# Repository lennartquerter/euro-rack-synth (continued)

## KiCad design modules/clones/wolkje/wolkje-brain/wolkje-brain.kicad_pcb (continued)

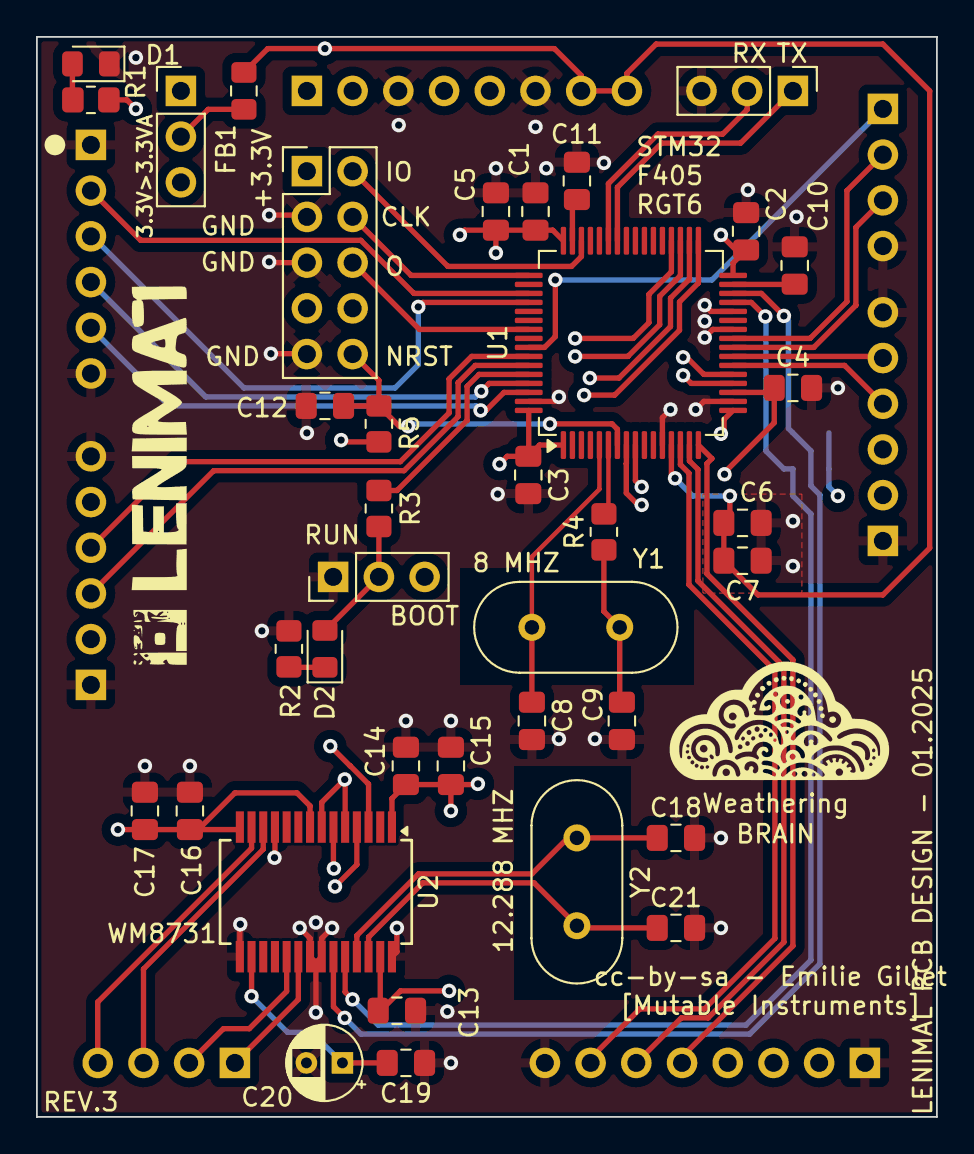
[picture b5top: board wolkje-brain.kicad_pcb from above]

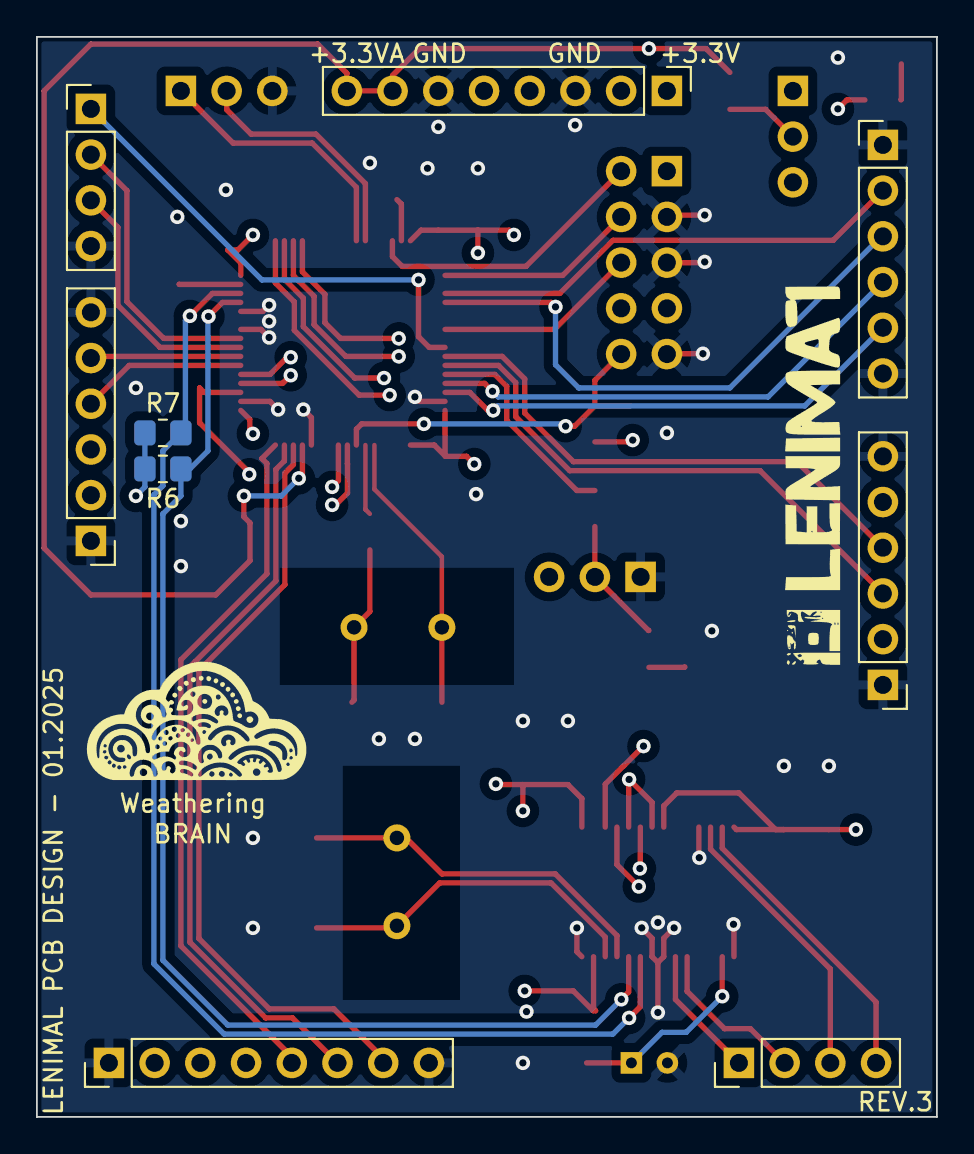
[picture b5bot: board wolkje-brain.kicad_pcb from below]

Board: 4 copper layers, 50.0 x 60.0 mm, 46 parts (9 on the bottom side), 51 nets.

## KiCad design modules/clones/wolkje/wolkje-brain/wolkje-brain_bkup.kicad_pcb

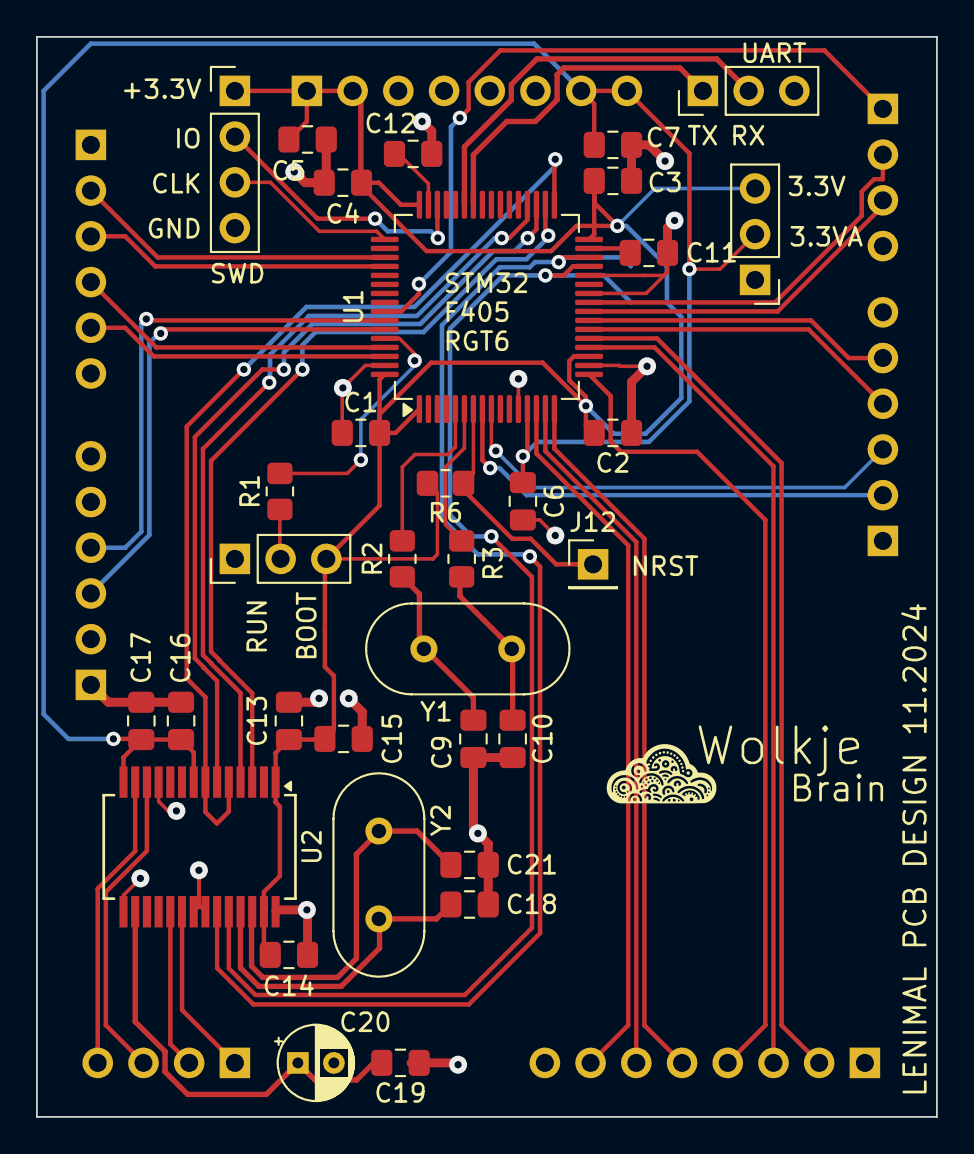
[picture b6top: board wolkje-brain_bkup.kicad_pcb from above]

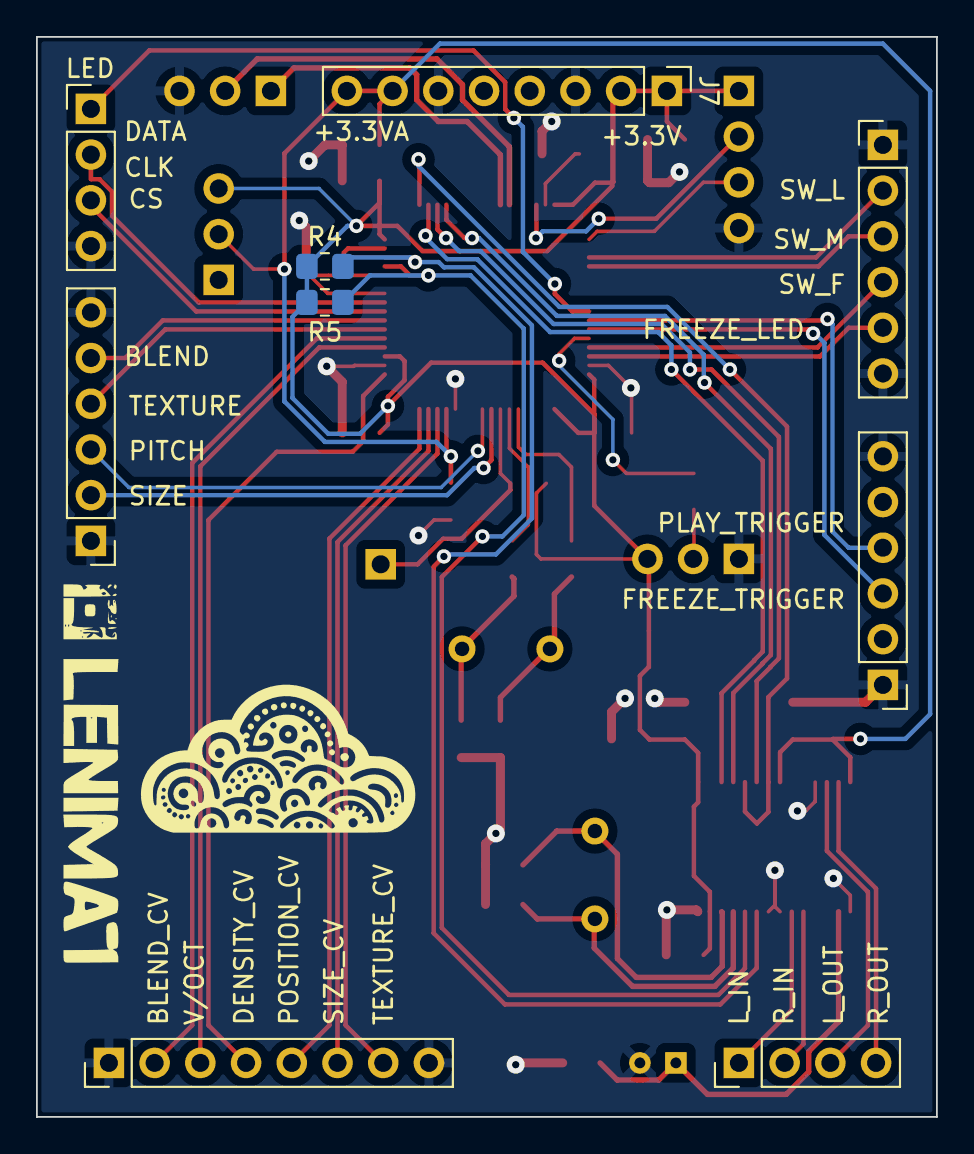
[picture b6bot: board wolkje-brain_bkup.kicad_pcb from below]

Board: 2 copper layers, 50.0 x 60.0 mm, 42 parts (9 on the bottom side), 48 nets.

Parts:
C1, C2, C3, C4, C6, C13, C14, C16: 100nF; C_0805_2012Metric_Pad1.18x1.45mm_HandSolder
C5, C15, C17: 10uF; C_0805_2012Metric_Pad1.18x1.45mm_HandSolder
C7, C19: 1uF; C_0805_2012Metric_Pad1.18x1.45mm_HandSolder
C9, C10, C18, C21: 18pF; C_0805_2012Metric_Pad1.18x1.45mm_HandSolder
C11, C12: 2.2uF; C_0805_2012Metric_Pad1.18x1.45mm_HandSolder
C20: 10uF; CP_Radial_D4.0mm_P2.00mm
J1: BOOT_RUN; PinHeader_1x03_P2.54mm_Vertical
J2: UART; PinHeader_1x03_P2.54mm_Vertical
J3: SWD; PinHeader_1x04_P2.54mm_Vertical
J4: AUDIO_IN_OUT; PinHeader_1x04_P2.54mm_Vertical
J5: LED_DRIVER; PinHeader_1x04_P2.54mm_Vertical
J6, J9, J10: Conn_01x06; PinHeader_1x06_P2.54mm_Vertical
J7: Power; PinHeader_1x08_P2.54mm_Vertical
J8: Conn_01x08; PinHeader_1x08_P2.54mm_Vertical
J11: V_VA_CONN; PinHeader_1x03_P2.54mm_Vertical
J12: RESET_PIN; PinHeader_1x01_P2.54mm_Vertical
R1, R6: 10K; R_0805_2012Metric_Pad1.20x1.40mm_HandSolder
R2, R3: 10R; R_0805_2012Metric_Pad1.20x1.40mm_HandSolder
R4, R5: 2K2; R_0805_2012Metric_Pad1.20x1.40mm_HandSolder
U1: STM32F405RGT6; LQFP-64_10x10mm_P0.5mm
U2: WM8731SEDS; SSOP-28_5.3x10.2mm_P0.65mm
Y1: 8MHZ; Crystal_HC49-U_Vertical
Y2: 12.288MHZ; Crystal_HC49-U_Vertical

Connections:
+3.3V: C1.2, C2.2, C3.2, C4.2, C5.2, C13.2, C14.2, C15.2, J1.3, J3.1, J7.1, J7.2, J11.3, R4.1, R5.2, R6.2, U1.1 (VBAT), U1.19 (VDD), U1.32 (VDD), U1.48 (VDD), U1.64 (VDD), U2.1 (DBVDD), U2.27 (DCVDD)
+3.3VA: C6.2, C7.2, C16.2, C17.2, J7.7, J7.8, J11.2, U1.13 (VDDA), U2.8 (HPVDD), U2.14 (AVDD)
/STM32/BLEND: J6.5, U1.23 (PA7)
/STM32/BLEND_CV: J8.2, U1.21 (PA5)
/STM32/BOOT0: R1.2, U1.60 (BOOT0)
/STM32/DENSITY_CV: J8.4, U1.17 (PA3)
/STM32/FREEZE_LED: J10.5, U1.62 (PB9)
/STM32/FREEZE_TRIGGER: J9.3, U1.59 (PB7)
/STM32/HSC_IN: R2.2, U1.5 (PH0)
/STM32/HSC_OUT: R3.2, U1.6 (PH1)
/STM32/I2C_SCL: R5.1, U1.29 (PB10), U2.24 (SCLK)
/STM32/I2C_SDA: R4.2, U1.30 (PB11), U2.23 (SDIN)
/STM32/I2S_LRCK: U1.33 (PB12), U2.5 (DACLRC), U2.7 (ADCLRC)
/STM32/I2S_SCK: U1.34 (PB13), U2.3 (BCLK)
/STM32/I2S_SIN: U1.35 (PB14), U2.6 (ADCDAT)
/STM32/I2S_SOUT: U1.36 (PB15), U2.4 (DACDAT)
/STM32/LED_CLK: J5.2, U1.25 (PC5)
/STM32/LED_DATA: J5.1, U1.57 (PB5)
/STM32/LED_ENABLE: J5.3, U1.24 (PC4)
/STM32/NRST: J12.1, R6.1, U1.7 (NRST)
/STM32/PITCH: J6.3, U1.9 (PC1)
/STM32/PLAY_TRIGGER: J9.4, U1.58 (PB6)
/STM32/POSITION_CV: J8.5, U1.16 (PA2)
/STM32/RX: J2.2, U1.43 (PA10)
/STM32/SIZE: J6.2, U1.8 (PC0)
/STM32/SIZE_CV: J8.6, U1.15 (PA1)
/STM32/SWD_CLK: J3.3, U1.49 (PA14)
/STM32/SWD_IO: J3.2, U1.46 (PA13)
/STM32/SW_FREEZE: J10.4, U1.61 (PB8)
/STM32/SW_LOAD: J10.2, U1.51 (PC10)
/STM32/SW_MODE: J10.3, U1.52 (PC11)
/STM32/TEXTURE: J6.4, U1.22 (PA6)
/STM32/TEXTURE_CV: J8.7, U1.14 (PA0)
/STM32/TX: J2.1, U1.42 (PA9)
/STM32/VCAP_1: C11.1, U1.31 (VCAP_1)
/STM32/VCAP_2: C12.1, U1.47 (VCAP_2)
/STM32/V_OCT: J8.3, U1.20 (PA4)
/audio-codec/L_IN: J4.1, U2.20 (LLINEIN)
/audio-codec/L_OUT: J4.3, U2.12 (LOUT)
/audio-codec/R_IN: J4.2, U2.19 (RLINEIN)
/audio-codec/R_OUT: J4.4, U2.13 (ROUT)
GNDREF: C1.1, C2.1, C3.1, C4.1, C5.1, C6.1, C7.1, C9.2, C10.2, C11.2, C12.2, C13.1, C14.1, C15.1, C16.1, C17.1, C18.2, C19.1, C20.2, C21.2, J1.1, J2.3, J3.4, J5.4, J6.1, J6.6, J7.3, J7.6, J8.1, J8.8, J9.1, J9.6, J10.1, J10.6, U1.12 (VSSA), U1.18 (VSS), U1.26 (PB0), U1.28 (PB2), U1.63 (VSS), U2.11 (HPGND), U2.15 (AGND), U2.21 (MODE), U2.22 (~CSB), U2.28 (DGND)
unnamed: C9.1, R2.1, Y1.1
unnamed: C10.1, R3.1, Y1.2
unnamed: J1.2, R1.1
unnamed: C19.2, C20.1, U2.16 (VMID)
unnamed: C18.1, U2.25 (XTI/MCLK), Y2.1
unnamed: C21.1, U2.26 (XTO), Y2.2
